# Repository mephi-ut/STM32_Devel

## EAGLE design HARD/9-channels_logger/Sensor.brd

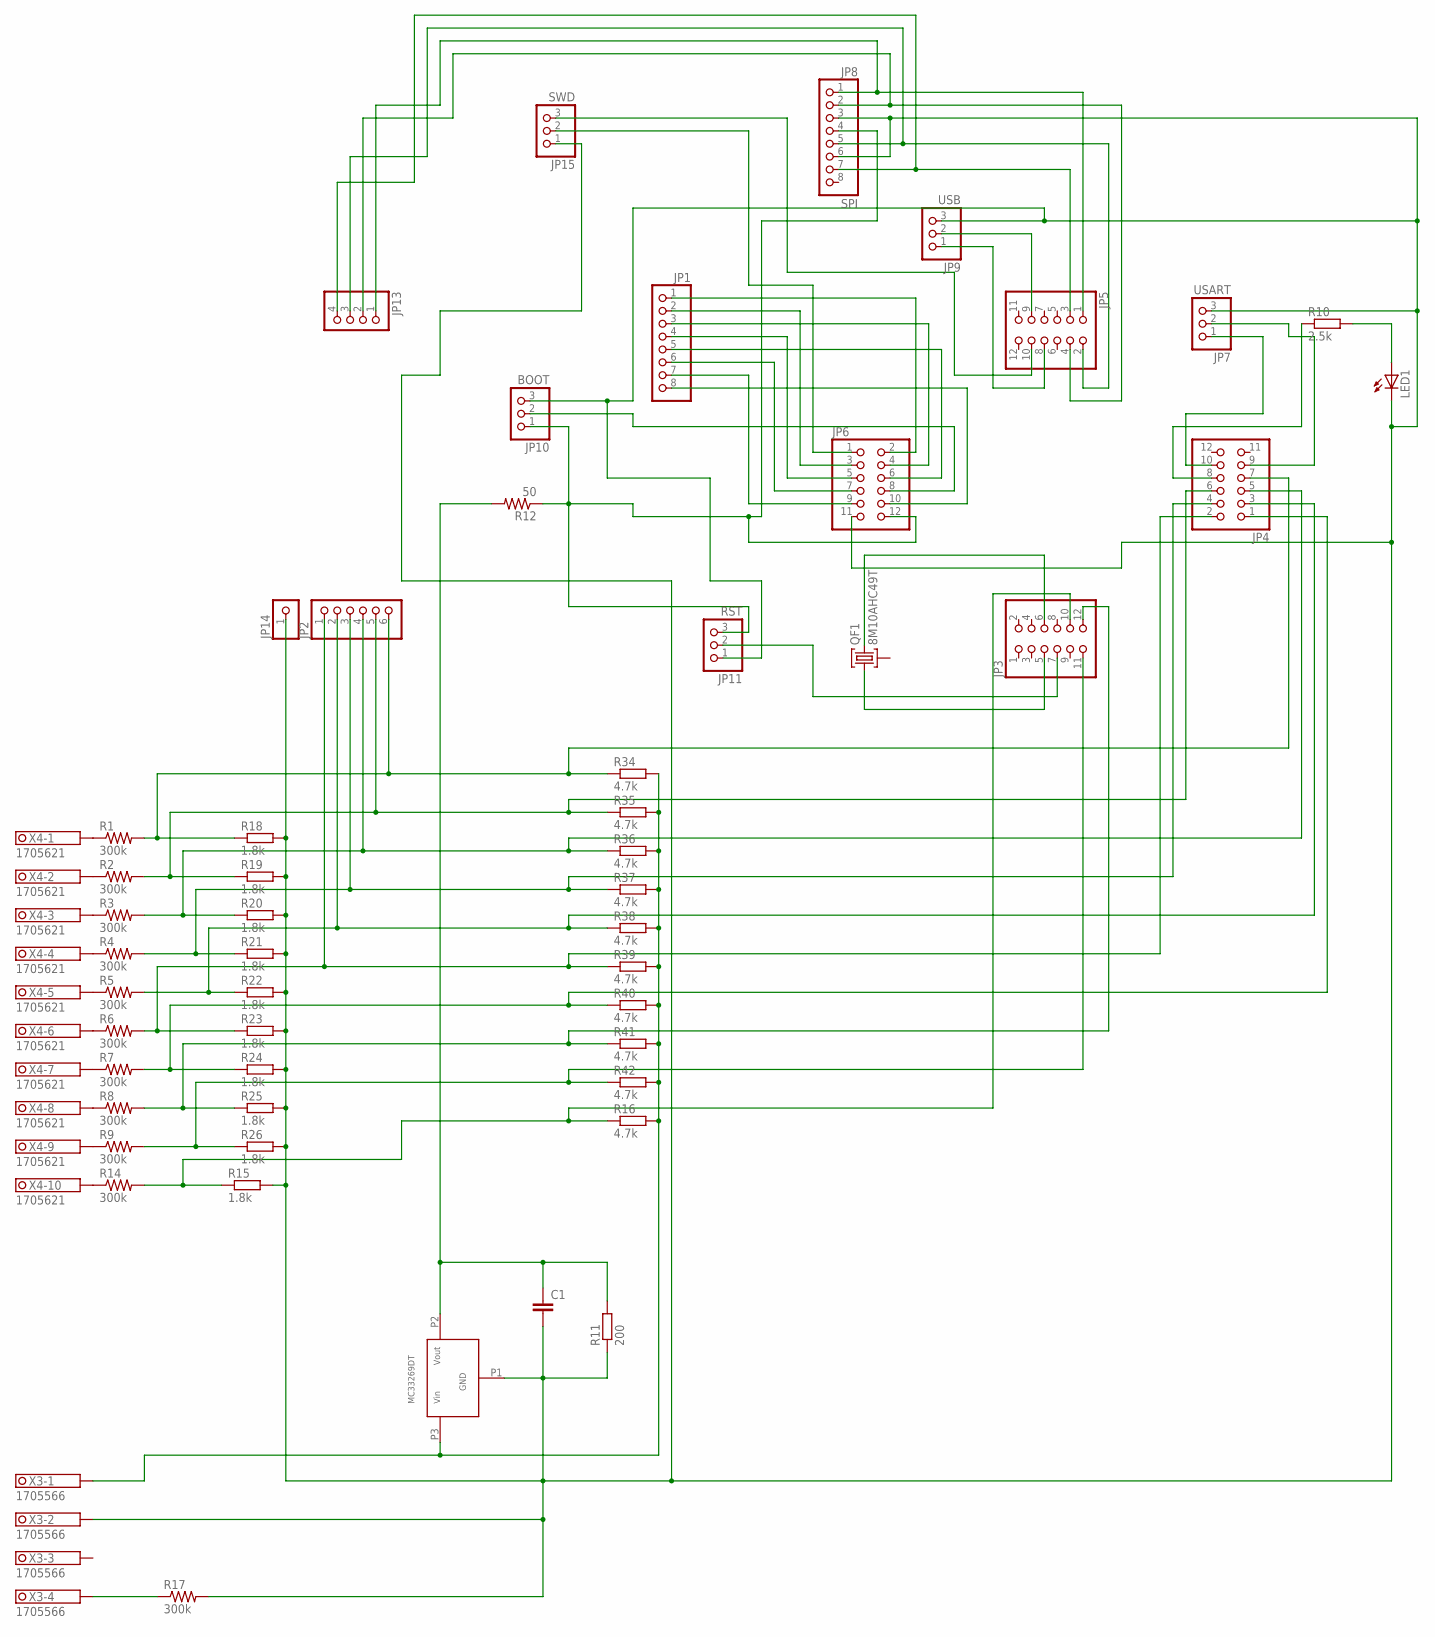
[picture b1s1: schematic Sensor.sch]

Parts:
C1: C2.5/6; C2.5-6
JP1: PINHD-1X8; 1X08
JP2: PINHD-1X6; 1X06
JP3, JP4, JP5, JP6: PINHD-2X6; 2X06
JP7: USART; 1X03
JP8: SPI; 1X08
JP9: USB; 1X03
JP10: BOOT; 1X03
JP11: RST; 1X03
JP13: PINHD-1X4; 1X04
JP14: PINHD-1X1; 1X01
JP15: SWD; 1X03
LED1: LED3MM
QF1: 8M10AHC49T; HC49U
R1, R2, R3, R4, R5, R6, R7, R8, R9, R14, R17: 300k; 0207/15
R10: 2.5k; M1206
R11: 200; R1206
R12: 50; 0207/15
R15, R18, R19, R20, R21, R22, R23, R24, R25, R26: 1.8k; R1206
R16, R34, R35, R36, R37, R38, R39, R40, R41, R42: 4.7k; R1206
U$3: MC33269DT
X3: 1705566
X4: 1705621

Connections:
unnamed: JP3.10, R14.2, R15.1, R16.1
unnamed: R17.1, X3.4.1, X3.4.2
unnamed: R1.1, X4.1.1, X4.1.2
unnamed: R2.1, X4.2.1, X4.2.2
unnamed: R3.1, X4.3.1, X4.3.2
unnamed: R4.1, X4.4.1, X4.4.2
unnamed: R5.1, X4.5.1, X4.5.2
unnamed: R6.1, X4.6.1, X4.6.2
unnamed: R7.1, X4.7.1, X4.7.2
unnamed: JP3.5, QF1.1
unnamed: JP3.6, QF1.3
unnamed: JP3.7, JP11.2
unnamed: R8.1, X4.8.1, X4.8.2
unnamed: LED1.A, R10.2
unnamed: JP4.8, R10.1
unnamed: R16.2, R34.2, R35.2, R36.2, R37.2, R38.2, R39.2, R40.2, R41.2, R42.2, U$3.P3 (VIN), X3.1.1, X3.1.2
unnamed: JP2.6, JP4.7, R1.2, R18.1, R34.1
unnamed: JP2.5, JP4.6, R2.2, R19.1, R35.1
unnamed: JP2.4, JP4.5, R3.2, R20.1, R36.1
unnamed: JP2.3, JP4.4, R4.2, R21.1, R37.1
unnamed: JP2.2, JP4.3, R5.2, R22.1, R38.1
unnamed: JP2.1, JP4.2, R6.2, R23.1, R39.1
unnamed: JP4.1, R7.2, R24.1, R40.1
unnamed: JP3.12, R8.2, R25.1, R41.1
unnamed: JP3.11, R9.2, R26.1, R42.1
unnamed: JP4.9, JP7.2
unnamed: JP4.10, JP7.1
unnamed: C1.2, JP6.11, JP7.3, JP8.3, JP8.6, JP9.3, JP10.3, JP11.1, JP14.1, JP15.1, LED1.K (C), R11.1, R15.2, R17.2, R18.2, R19.2, R20.2, R21.2, R22.2, R23.2, R24.2, R25.2, R26.2, U$3.P1 (GND), X3.2.1, X3.2.2
unnamed: C1.1, R11.2, R12.2, U$3.P2 (VOUT)
unnamed: JP5.8, JP9.1
unnamed: JP5.9, JP9.2
unnamed: JP5.10, JP15.3
unnamed: JP6.1, JP15.2
unnamed: JP5.1, JP8.1, JP13.1
unnamed: JP5.4, JP8.2, JP13.2
unnamed: JP5.2, JP8.5, JP13.3
unnamed: JP5.3, JP8.7, JP13.4
unnamed: JP6.12, JP8.4, JP10.1, JP11.3, R12.1
unnamed: JP1.1, JP6.2
unnamed: JP1.2, JP6.3
unnamed: JP1.3, JP6.4
unnamed: JP1.4, JP6.5
unnamed: JP1.5, JP6.6
unnamed: JP1.6, JP6.7
unnamed: JP1.7, JP6.9
unnamed: JP1.8, JP6.10
unnamed: R9.1, X4.9.1, X4.9.2
unnamed: R14.1, X4.10.1, X4.10.2
unnamed: JP6.8, JP10.2

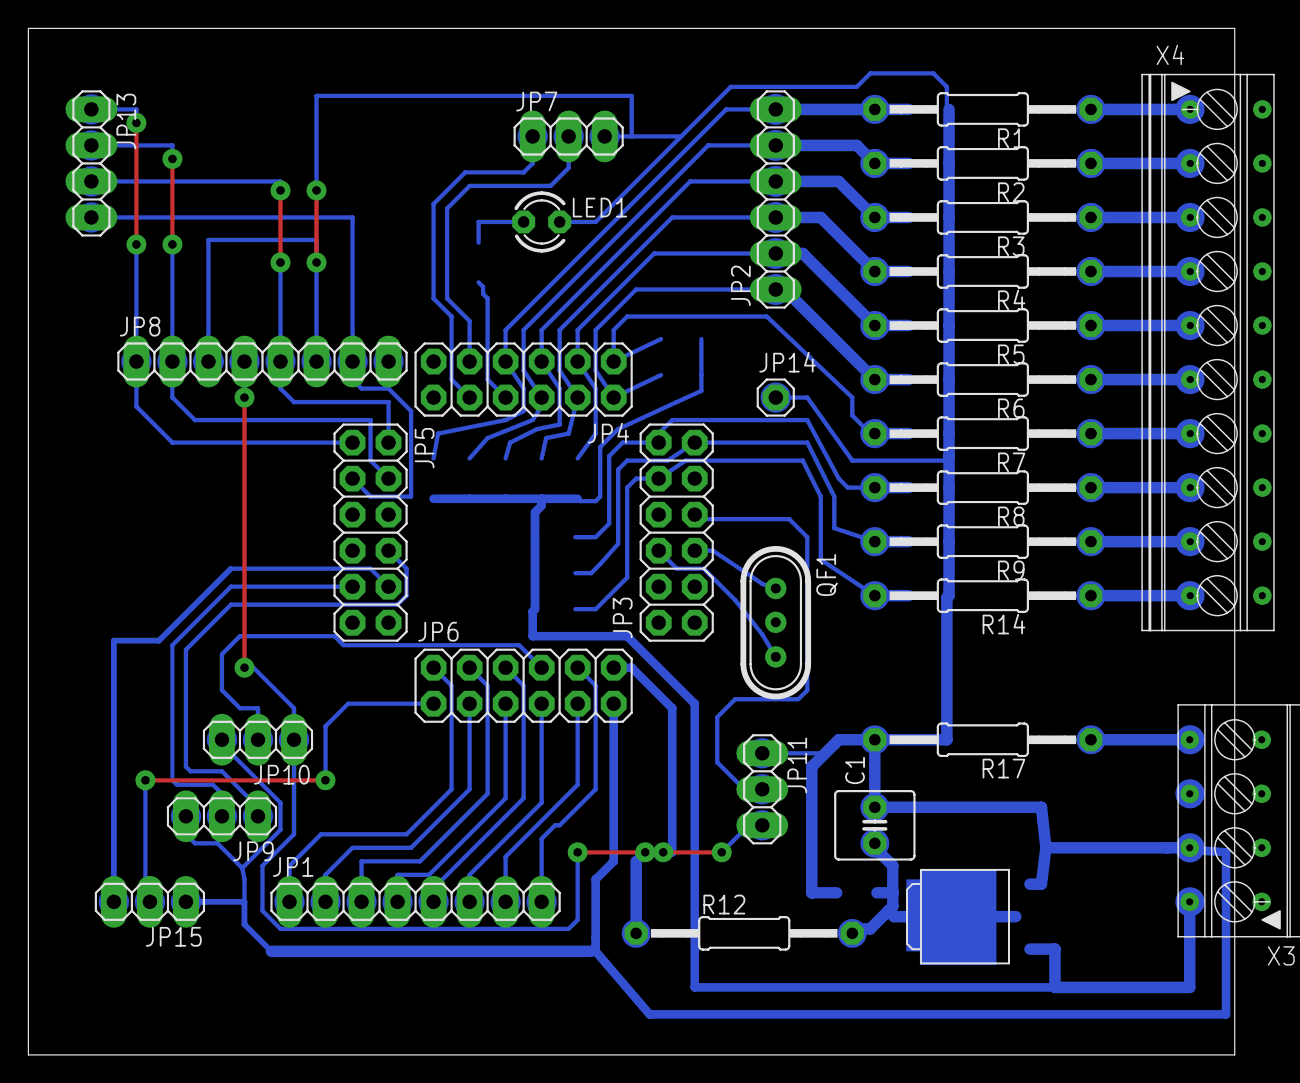
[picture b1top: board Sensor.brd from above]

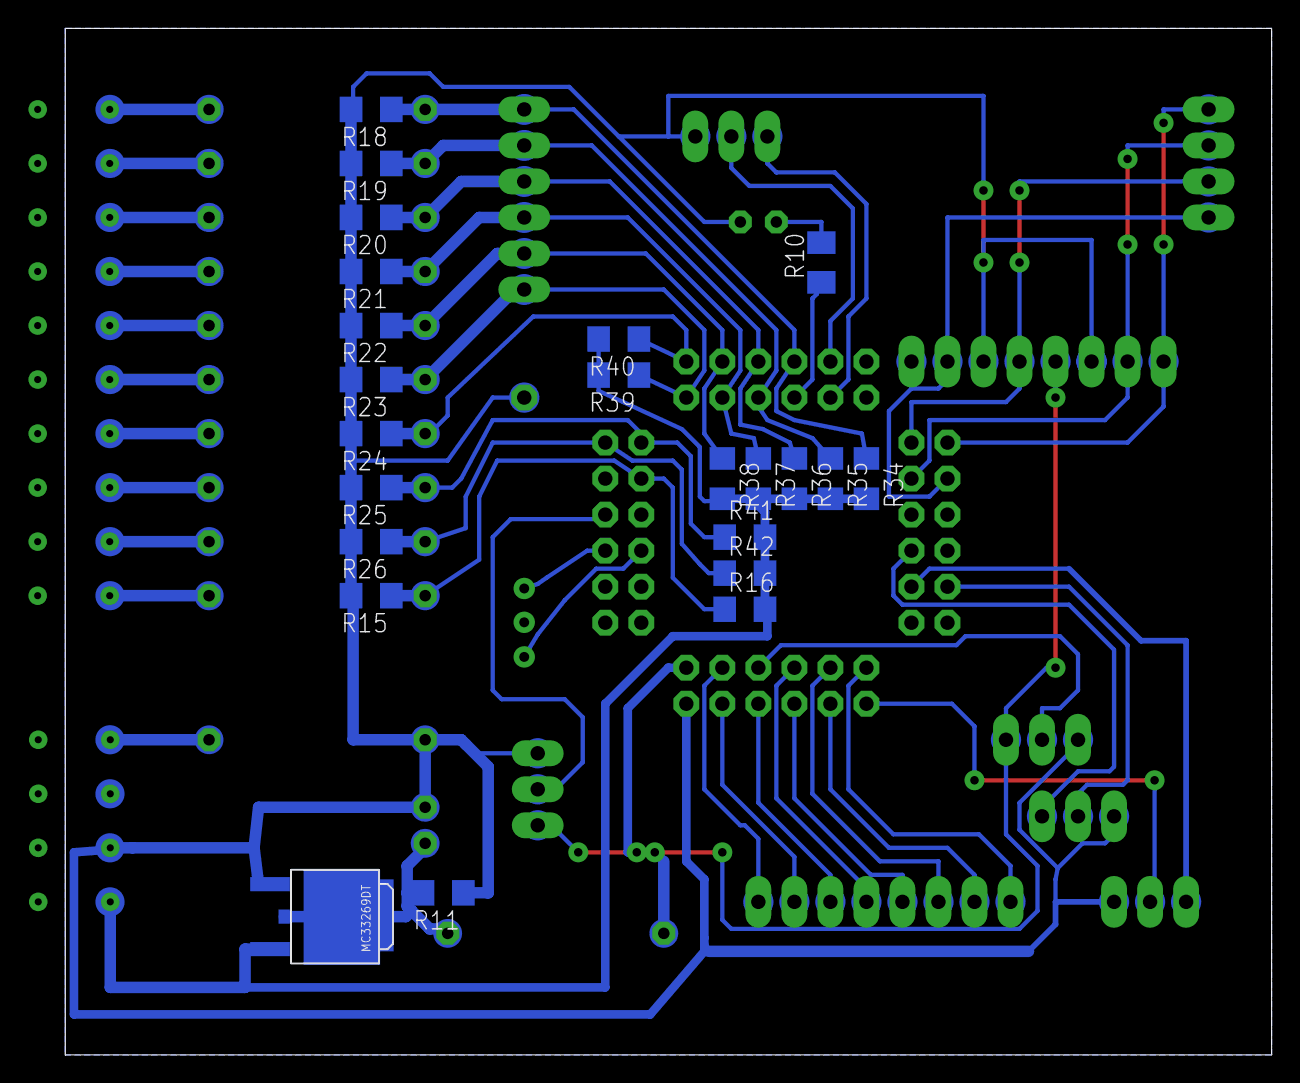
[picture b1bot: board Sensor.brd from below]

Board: 2 copper layers, 85.1 x 72.4 mm, 54 parts (23 on the bottom side), 49 nets.

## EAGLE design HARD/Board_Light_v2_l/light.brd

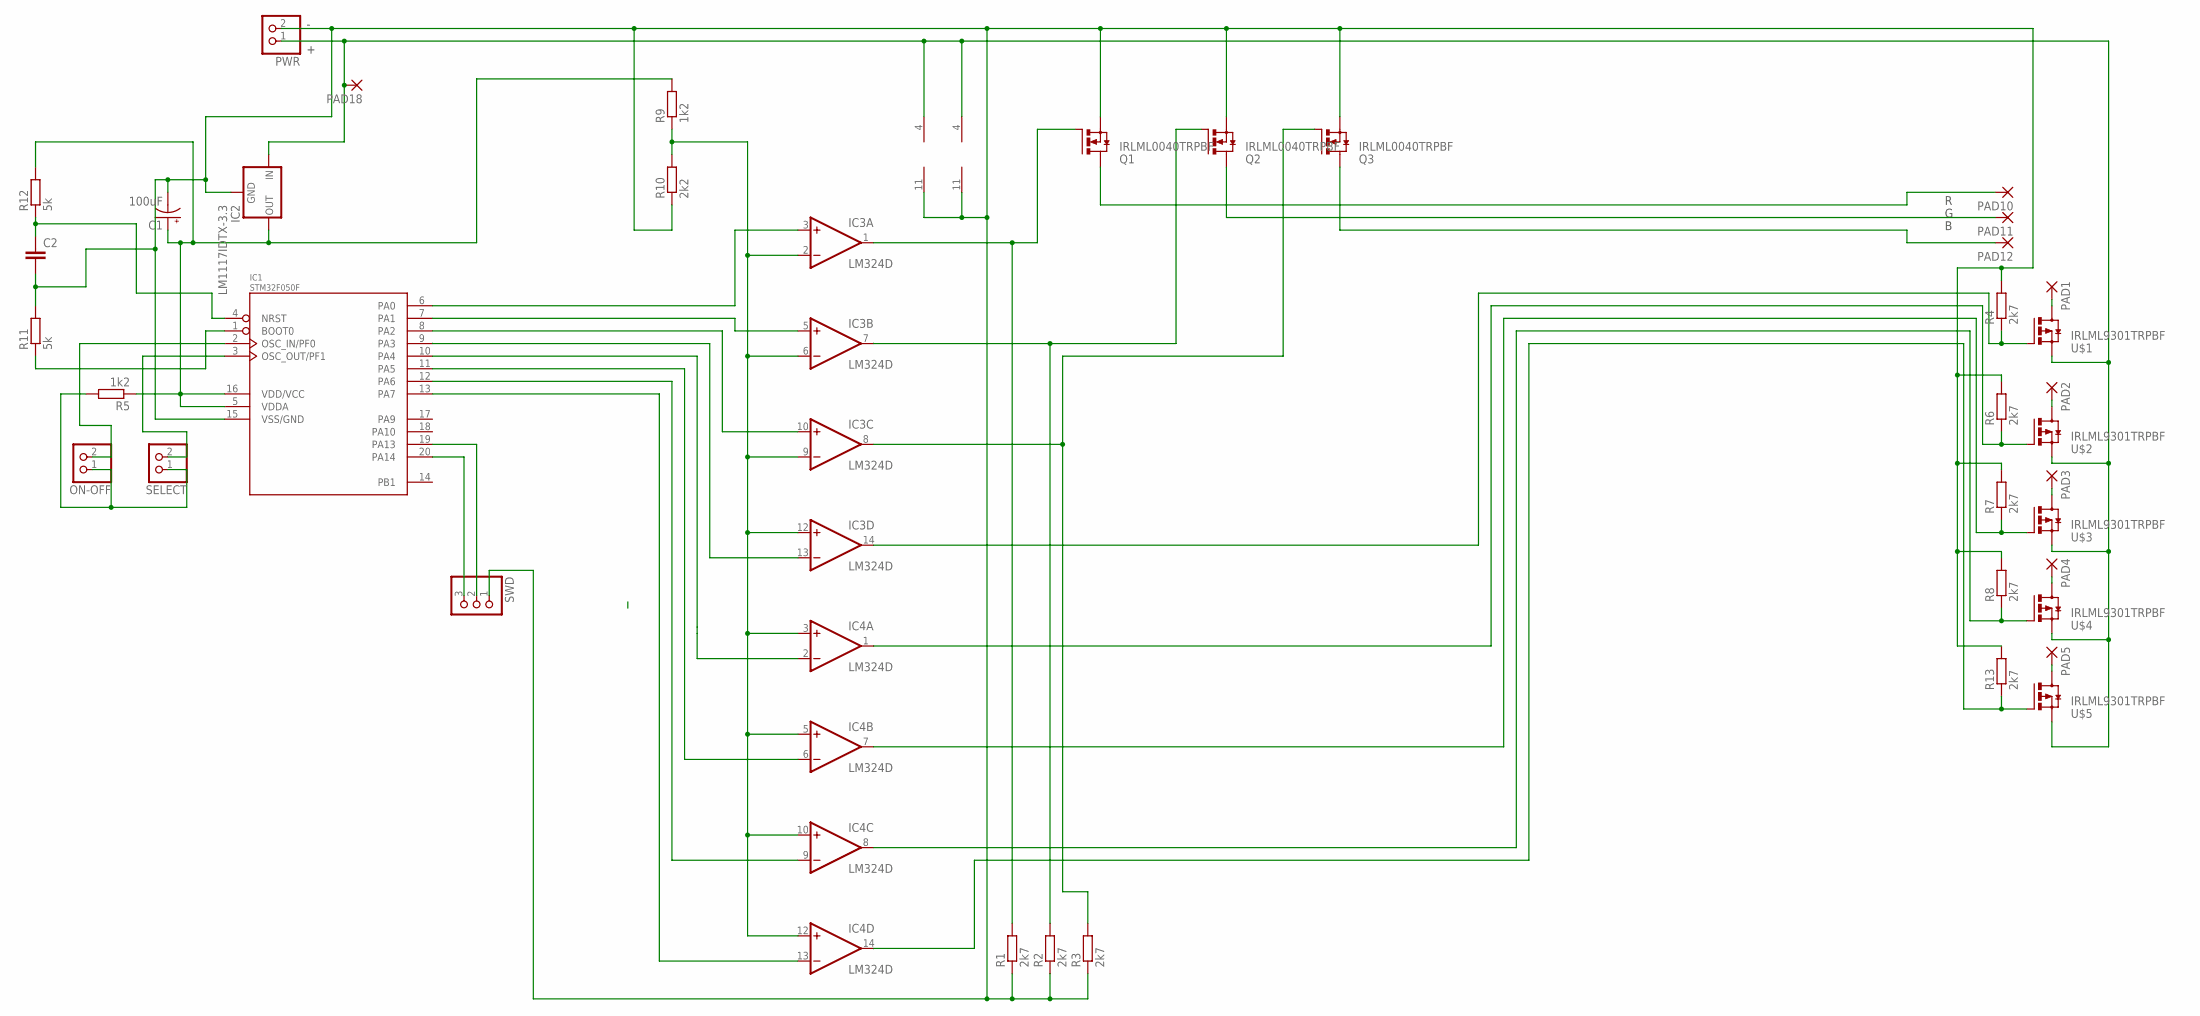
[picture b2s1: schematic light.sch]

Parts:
C1: 100uF; SMC_D
C2: C-EUC1206; C1206
IC1: STM32F050F; TSSOP20
IC2: LM1117IDTX-3.3; TO252
IC3, IC4: LM324D; SO14
ON-OFF: PINHD-1X2; 1X02
PAD1, PAD2, PAD3, PAD4, PAD5, PAD10, PAD11, PAD12, PAD18: SMD2; SMD1,27-2,54
PWR: PINHD-1X2; 1X02
Q1, Q2, Q3: IRLML0040TRPBF; MICRO3
R1, R2, R3, R4, R6, R7, R8, R13: 2k7; M1206
R5, R9: 1k2; M1206
R10: 2k2; M1206
R11, R12: 5k; M1206
SELECT: PINHD-1X2; 1X02
SWD: PINHD-1X3; 1X03
U$1, U$2, U$3, U$4, U$5: IRLML9301TRPBF; MICRO3

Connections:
unnamed: IC3.8 (OUT), Q3.1 (G), R3.2
unnamed: IC3.7 (OUT), Q2.1 (G), R2.2
unnamed: IC3.14 (OUT), R4.1, U$1.1 (G)
unnamed: IC4.1 (OUT), R6.1, U$2.1 (G)
unnamed: IC2.2 (IN), IC3.4 (V+), IC4.4 (V+), PAD18.1, PWR.1, U$1.2 (S), U$2.2 (S), U$3.2 (S), U$4.2 (S), U$5.2 (S)
unnamed: ON-OFF.1, R5.2, SELECT.1
unnamed: PAD10.1, Q1.3 (D)
unnamed: PAD11.1, Q2.3 (D)
unnamed: PAD12.1, Q3.3 (D)
unnamed: IC4.7 (OUT), R7.1, U$3.1 (G)
unnamed: IC4.8 (OUT), R8.1, U$4.1 (G)
unnamed: IC4.14 (OUT), R13.1, U$5.1 (G)
unnamed: IC1.6 (PA0), IC3.3 (+IN)
unnamed: IC1.7 (PA1), IC3.5 (+IN)
unnamed: IC1.8 (PA2), IC3.10 (+IN)
unnamed: IC1.9 (PA3), IC3.13 (-IN)
unnamed: IC1.10 (PA4), IC4.2 (-IN)
unnamed: IC1.11 (PA5), IC4.6 (-IN)
unnamed: IC1.12 (PA6), IC4.9 (-IN)
unnamed: IC1.13 (PA7), IC4.13 (-IN)
unnamed: PAD1.1, U$1.3 (D)
unnamed: PAD2.1, U$2.3 (D)
unnamed: PAD3.1, U$3.3 (D)
unnamed: IC3.2 (-IN), IC3.6 (-IN), IC3.9 (-IN), IC3.12 (+IN), IC4.3 (+IN), IC4.5 (+IN), IC4.10 (+IN), IC4.12 (+IN), R9.1, R10.2
unnamed: PAD4.1, U$4.3 (D)
unnamed: PAD5.1, U$5.3 (D)
unnamed: C2.1, IC1.4 (NRST), R12.1
unnamed: IC1.1 (BOOT0), R11.1
unnamed: IC1.19 (PA13), SWD.2
unnamed: IC1.20 (PA14), SWD.3
unnamed: IC1.2 (OSC_IN/PF0), ON-OFF.2
unnamed: IC3.1 (OUT), Q1.1 (G), R1.2
unnamed: C1.+, IC1.5 (VDDA), IC1.16 (VDD/VCC), IC2.TAB (OUT), R5.1, R9.2, R12.2
unnamed: C1.-, C2.2, IC1.15 (VSS/GND), IC2.1 (GND), IC3.11 (V-), IC4.11 (V-), PWR.2, Q1.2 (S), Q2.2 (S), Q3.2 (S), R1.1, R2.1, R3.1, R4.2, R6.2, R7.2, R8.2, R10.1, R11.2, R13.2, SWD.1
unnamed: IC1.3 (OSC_OUT/PF1), SELECT.2

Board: 2 copper layers, 40 parts (3 on the bottom side), 35 nets, no tracks yet.

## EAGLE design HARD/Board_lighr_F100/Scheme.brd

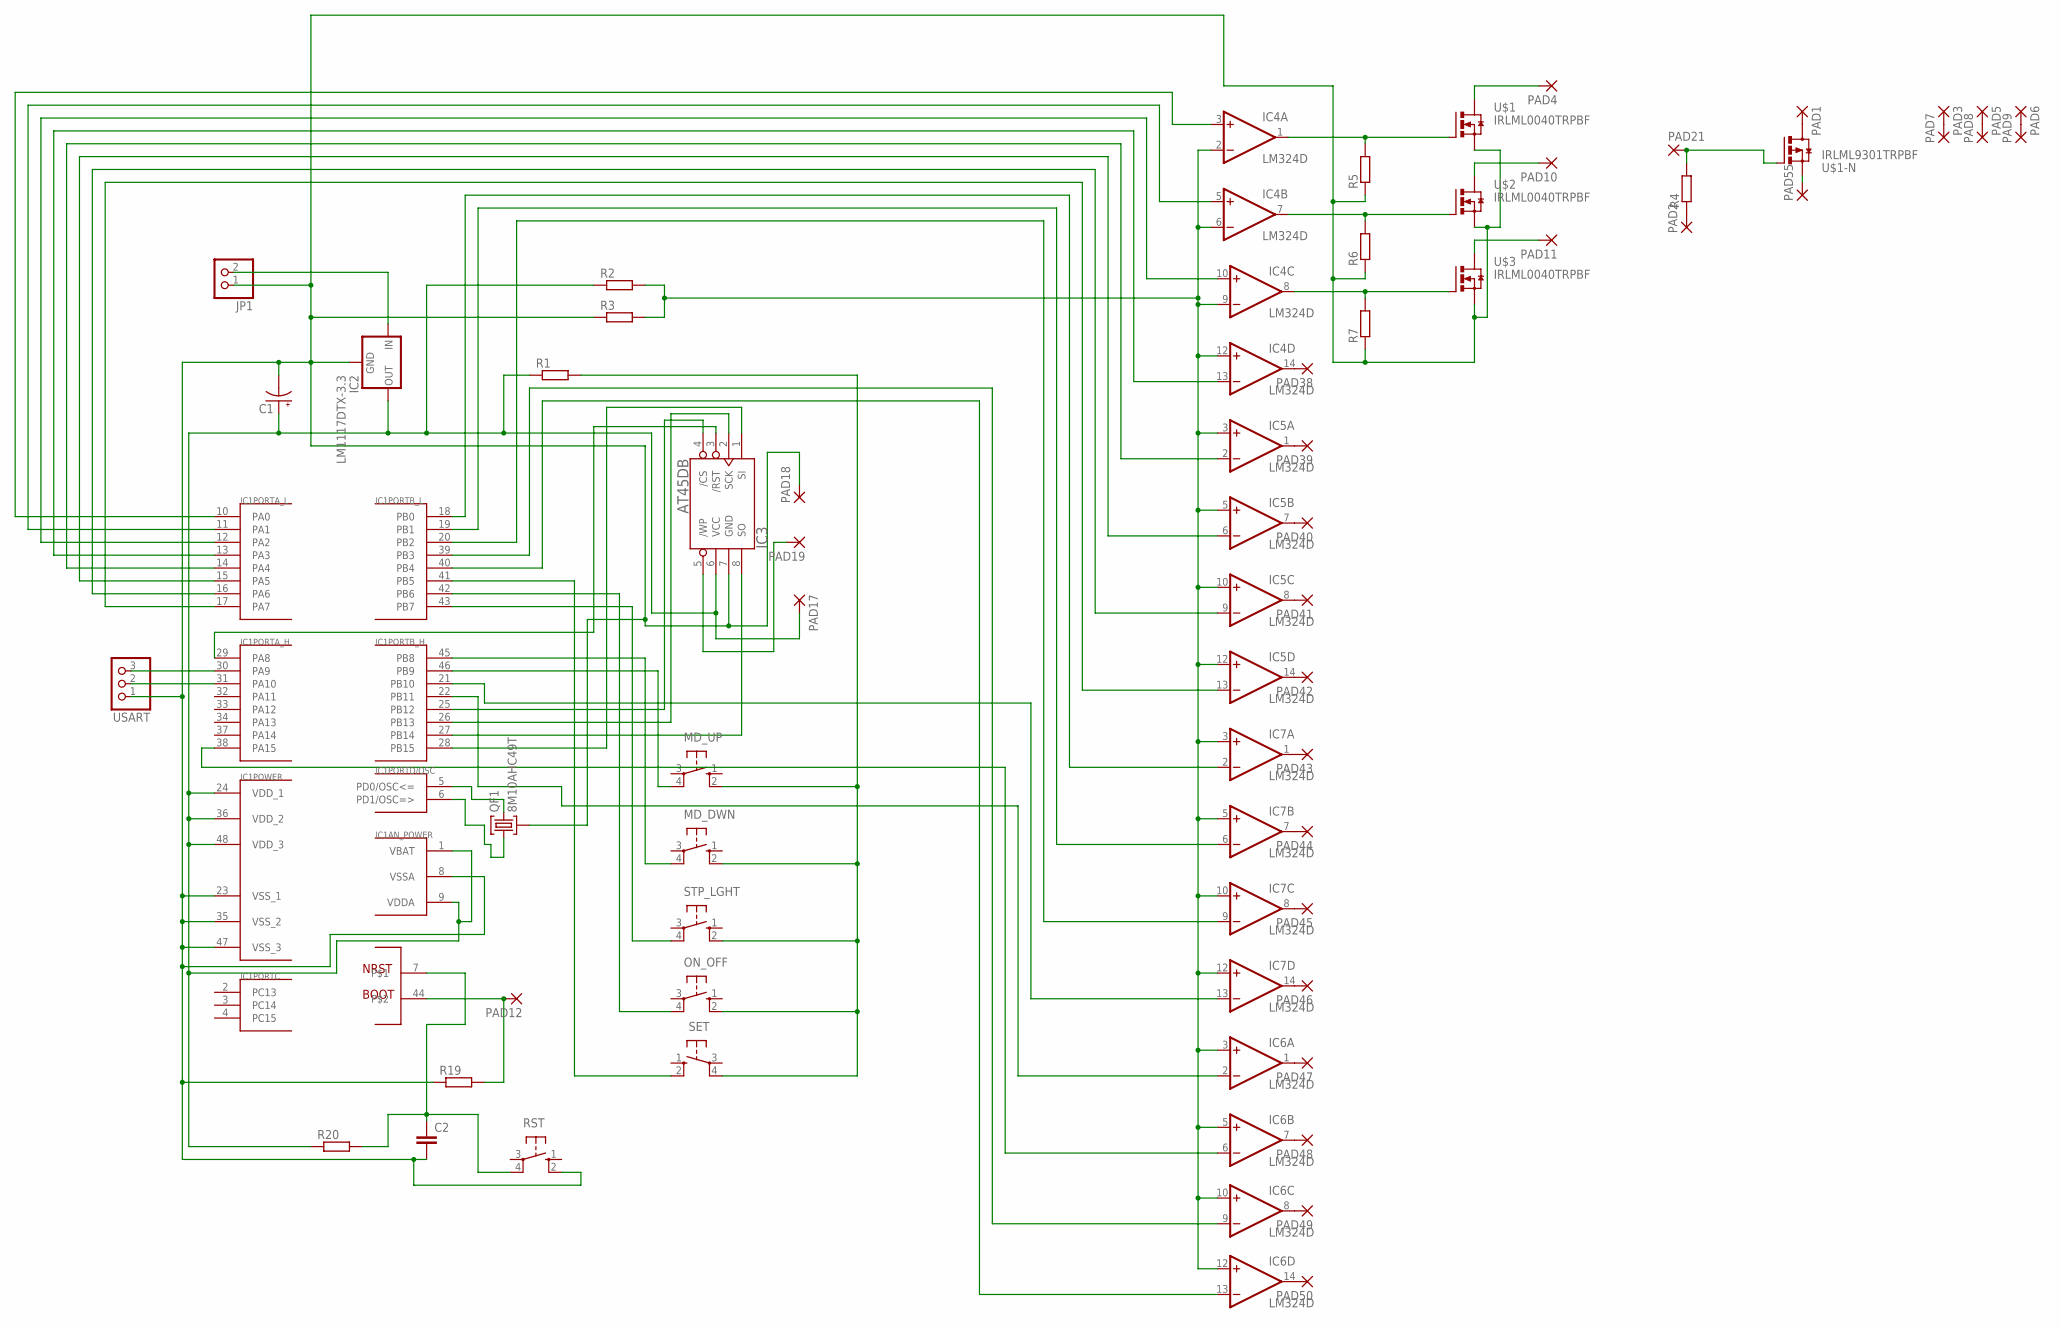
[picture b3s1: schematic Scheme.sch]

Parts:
C1: CPOL-USSMCD; SMC_D
C2: C-EUC0805; C0805
IC1: STM32F10XCXT6; TQFP48
IC2: LM1117DTX-3.3; TO252
IC3: AT45DB-S; SOIC8_208MIL
IC4, IC5, IC6, IC7: LM324D; SO14
JP1: PINHD-1X2; 1X02
MD_DWN: 40-XX; B3F-40XX
MD_UP: 40-XX; B3F-40XX
ON_OFF: 40-XX; B3F-40XX
PAD1, PAD2, PAD3, PAD4, PAD5, PAD6, PAD7, PAD8, PAD9, PAD10, PAD11, PAD12, PAD17, PAD18, PAD19, PAD21, PAD38, PAD39, PAD40, PAD41, PAD42, PAD43, PAD44, PAD45, PAD46, PAD47, PAD48, PAD49, PAD50, PAD55: SMD2; SMD1,27-2,54
QF1: 8M10AHC49T; HC49U
R1, R2, R3, R4, R5, R6, R7, R19, R20: R-EU_R1206; R1206
RST: 40-XX; B3F-40XX
SET: 40-XX; B3F-40XX
STP_LGHT: 40-XX; B3F-40XX
U$1, U$2, U$3: IRLML0040TRPBF; MICRO3
U$1-N: IRLML9301TRPBF; MICRO3
USART: PINHD-1X3; 1X03

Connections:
unnamed: PAD2.1, R4.1
unnamed: C1.-, C2.2, IC1.8 (VSSA), IC1.23 (VSS_1), IC1.35 (VSS_2), IC1.47 (VSS_3), IC2.1 (GND), IC3.7 (GND), JP1.1, PAD18.1, QF1.2, R3.1, R5.1, R6.1, R7.1, R19.1, RST.2 (S1), U$1.2 (S), U$2.2 (S), U$3.2 (S), USART.1
unnamed: PAD21.1, R4.2, U$1-N.1 (G)
unnamed: IC1.38 (PA15), IC6.6 (-IN)
unnamed: IC1.39 (PB3), IC6.9 (-IN)
unnamed: IC1.40 (PB4), IC6.13 (-IN)
unnamed: IC1.46 (PB9), MD_UP.4 (P1)
unnamed: IC1.45 (PB8), MD_DWN.4 (P1)
unnamed: IC1.43 (PB7), STP_LGHT.4 (P1)
unnamed: MD_DWN.2 (S1), MD_UP.2 (S1), ON_OFF.2 (S1), R1.2, SET.4 (P1), STP_LGHT.2 (S1)
unnamed: IC1.42 (PB6), ON_OFF.4 (P1)
unnamed: IC4.1 (OUT), R5.2, U$1.1 (G)
unnamed: IC4.7 (OUT), R6.2, U$2.1 (G)
unnamed: IC1.25 (PB12), IC3.4 (/CS)
unnamed: IC1.10 (PA0), IC4.3 (+IN)
unnamed: IC1.11 (PA1), IC4.5 (+IN)
unnamed: IC1.12 (PA2), IC4.10 (+IN)
unnamed: IC1.13 (PA3), IC4.13 (-IN)
unnamed: IC1.14 (PA4), IC5.2 (-IN)
unnamed: IC1.15 (PA5), IC5.6 (-IN)
unnamed: IC1.16 (PA6), IC5.9 (-IN)
unnamed: IC1.17 (PA7), IC5.13 (-IN)
unnamed: IC1.18 (PB0), IC7.2 (-IN)
unnamed: IC1.19 (PB1), IC7.6 (-IN)
unnamed: IC1.20 (PB2), IC7.9 (-IN)
unnamed: IC1.21 (PB10), IC7.13 (-IN)
unnamed: IC1.22 (PB11), IC6.2 (-IN)
unnamed: IC1.26 (PB13), IC3.2 (SCK)
unnamed: IC1.27 (PB14), IC3.8 (SO)
unnamed: IC1.28 (PB15), IC3.1 (SI)
unnamed: IC4.2 (-IN), IC4.6 (-IN), IC4.9 (-IN), IC4.12 (+IN), IC5.3 (+IN), IC5.5 (+IN), IC5.10 (+IN), IC5.12 (+IN), IC6.3 (+IN), IC6.5 (+IN), IC6.10 (+IN), IC6.12 (+IN), IC7.3 (+IN), IC7.5 (+IN), IC7.10 (+IN), IC7.12 (+IN), R2.2, R3.2
unnamed: C1.+, IC1.1 (VBAT), IC1.9 (VDDA), IC1.24 (VDD_1), IC1.36 (VDD_2), IC1.48 (VDD_3), IC2.TAB (OUT), IC3.6 (VCC), PAD17.1, R1.1, R2.1, R20.1
unnamed: IC4.8 (OUT), R7.2, U$3.1 (G)
unnamed: PAD1.1, U$1-N.3 (D)
unnamed: IC1.41 (PB5), SET.2 (S1)
unnamed: PAD3.1, PAD7.1
unnamed: PAD5.1, PAD8.1
unnamed: PAD6.1, PAD9.1
unnamed: IC1.30 (PA9), USART.3
unnamed: PAD4.1, U$1.3 (D)
unnamed: PAD10.1, U$2.3 (D)
unnamed: PAD11.1, U$3.3 (D)
unnamed: IC1.31 (PA10), USART.2
unnamed: IC1.44, PAD12.1, R19.2
unnamed: IC1.29 (PA8), IC3.3 (/RST)
unnamed: C2.1, IC1.7, R20.2, RST.4 (P1)
unnamed: IC3.5 (/WP), PAD19.1
unnamed: IC1.5 (PD0/OSC<=), QF1.3
unnamed: IC1.6 (PD1/OSC=>), QF1.1
unnamed: IC4.14 (OUT), PAD38.1
unnamed: IC5.1 (OUT), PAD39.1
unnamed: IC5.7 (OUT), PAD40.1
unnamed: IC5.8 (OUT), PAD41.1
unnamed: IC5.14 (OUT), PAD42.1
unnamed: IC7.1 (OUT), PAD43.1
unnamed: IC7.7 (OUT), PAD44.1
unnamed: IC7.14 (OUT), PAD46.1
unnamed: IC6.1 (OUT), PAD47.1
unnamed: IC6.7 (OUT), PAD48.1
unnamed: IC6.8 (OUT), PAD49.1
unnamed: IC6.14 (OUT), PAD50.1
unnamed: IC7.8 (OUT), PAD45.1
unnamed: IC2.2 (IN), JP1.2
unnamed: PAD55.1, U$1-N.2 (S)
V+: IC4.4 (V+), IC5.4 (V+), IC6.4 (V+), IC7.4 (V+)
V-: IC4.11 (V-), IC5.11 (V-), IC6.11 (V-), IC7.11 (V-)

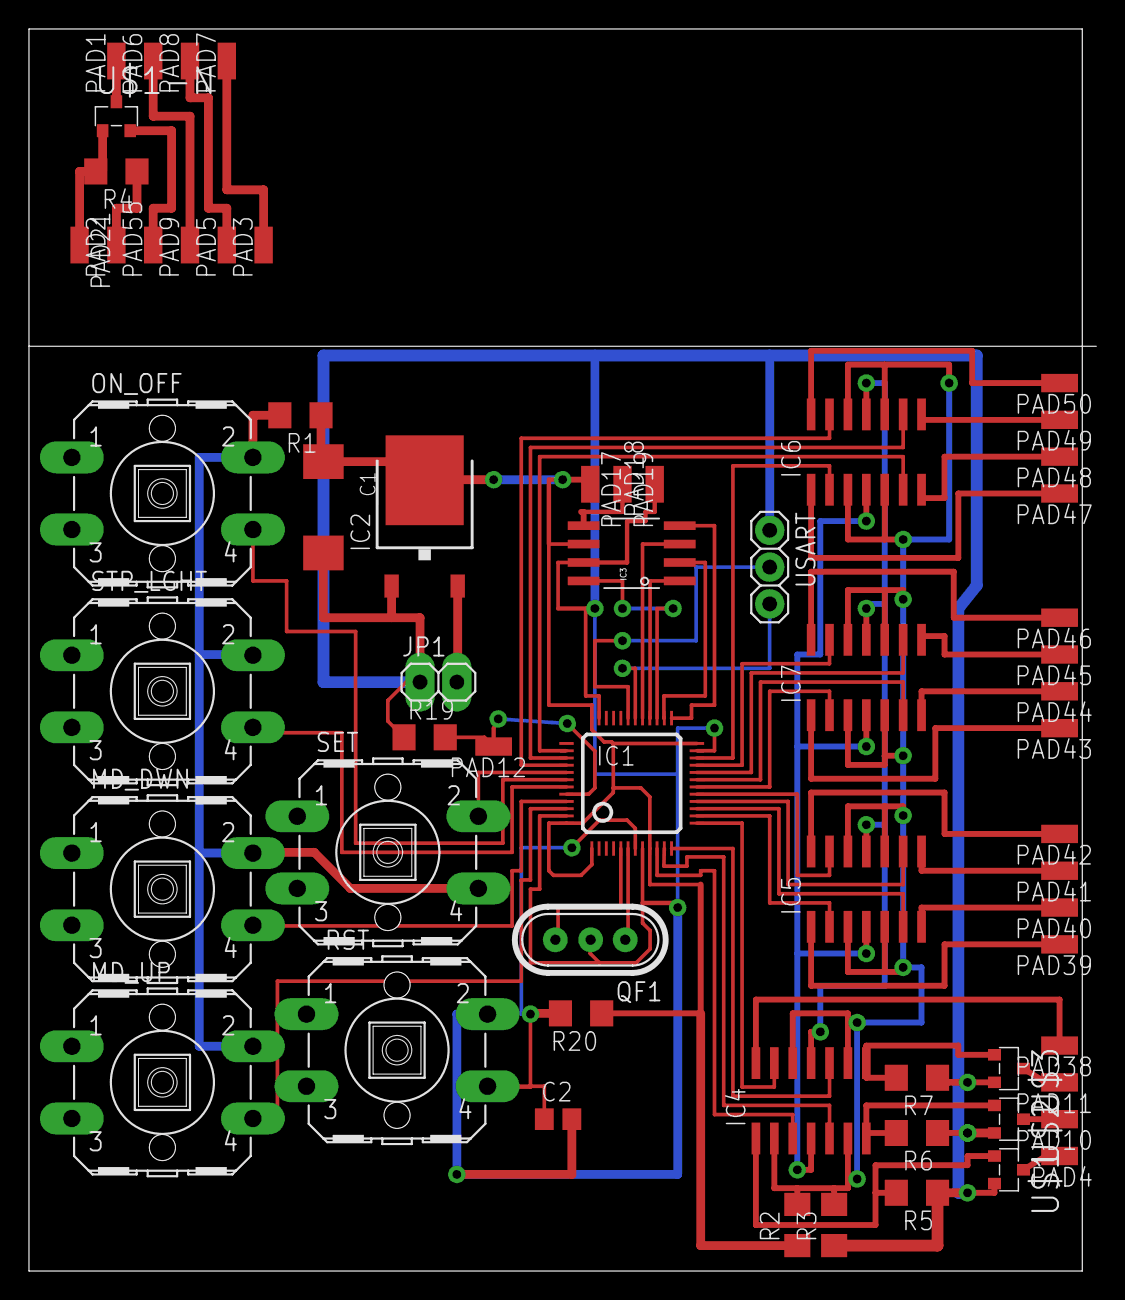
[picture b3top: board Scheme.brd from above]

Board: 2 copper layers, 73.7 x 85.7 mm, 61 parts (0 on the bottom side), 66 nets.

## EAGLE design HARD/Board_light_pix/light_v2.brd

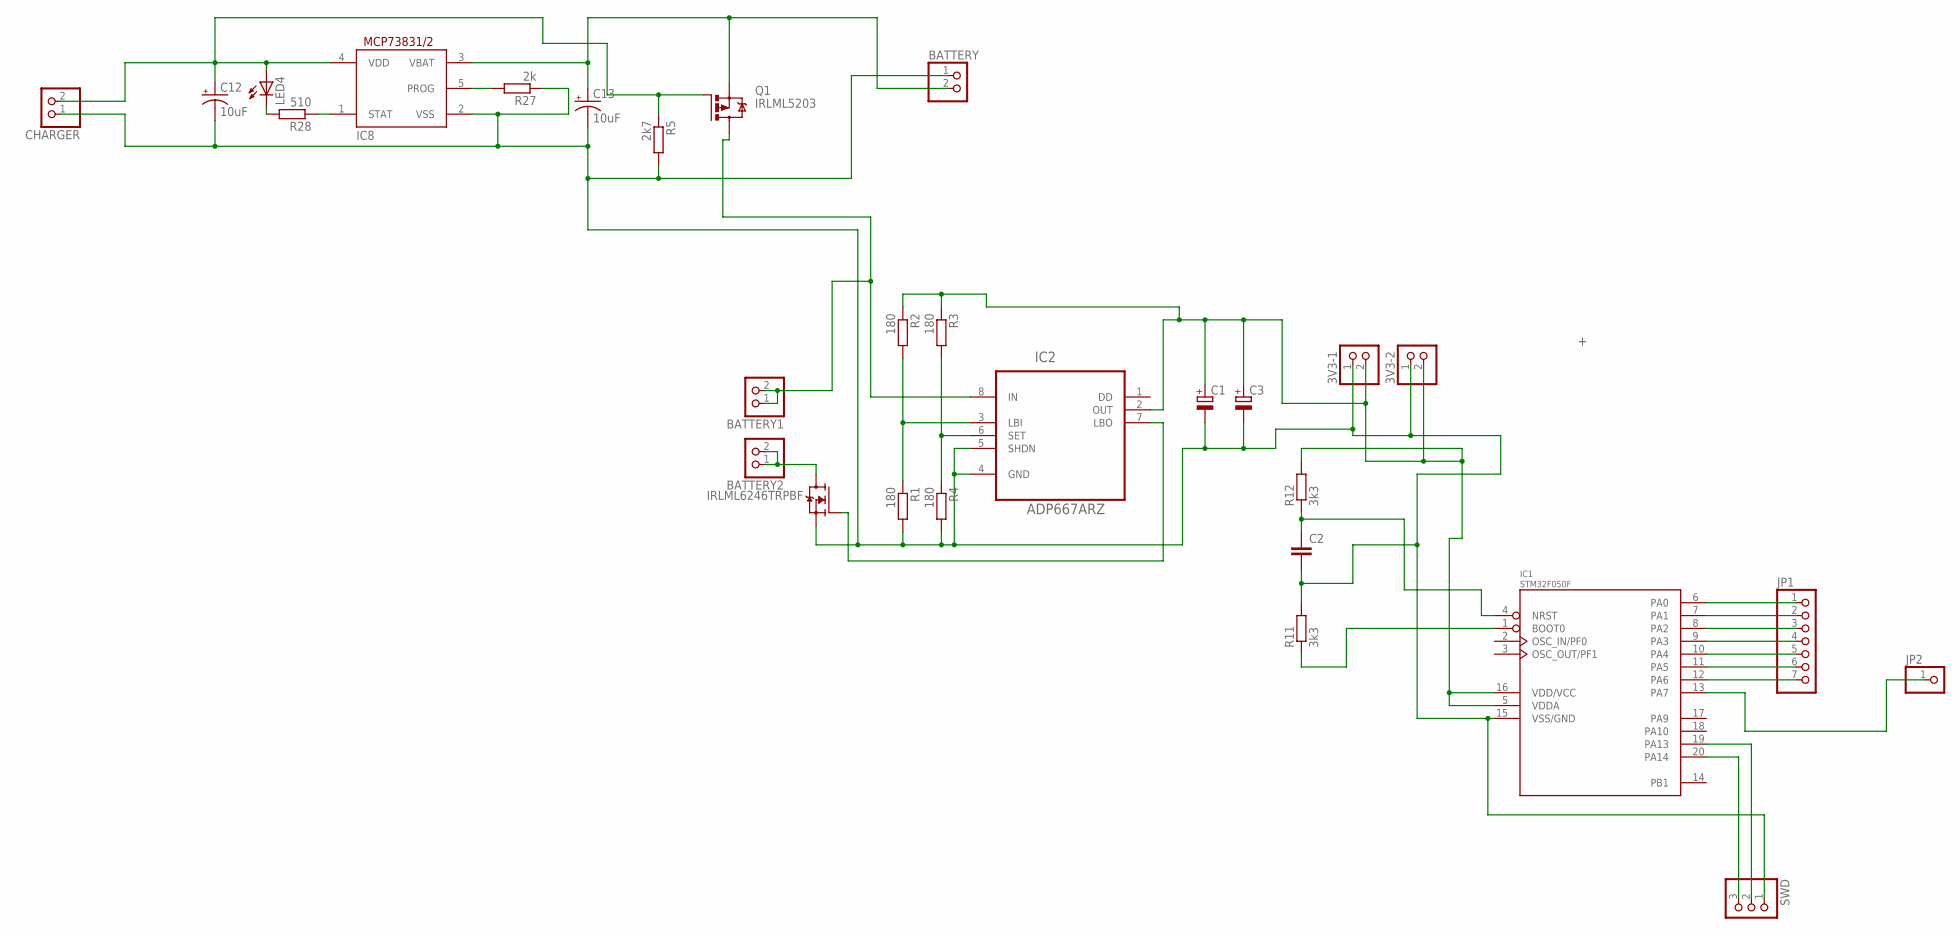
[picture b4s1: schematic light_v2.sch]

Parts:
3V3-1, 3V3-2: PINHD-1X2; 1X02
BATTERY, BATTERY1, BATTERY2: PINHD-1X2; 1X02
C1, C3: CPOL-EUSMCD; SMC_D
C2: C-EUC1206; C1206
C12, C13: 10uF; SMC_D
CHARGER: PINHD-1X2; 1X02
IC1: STM32F050F; TSSOP20
IC2: ADP667ARZ; SOIC127P600X175-8N
IC8: MCP73831/OT; SOT23-5L
IRLML6246TRPBF: MOSFET-N-SOT23; SOT23
JP1: PINHD-1X7; 1X07
JP2: PINHD-1X1; 1X01
LED4: LED; SMARTLED-TTW
Q1: IRLML5203; MICRO3
R1, R2, R3, R4: 180; M1206
R5: 2k7; M1206
R11, R12: 3k3; M1206
R27: 2k; M1206
R28: 510; M1206
SWD: PINHD-1X3; 1X03

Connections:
unnamed: IC1.6 (PA0), JP1.1
unnamed: IC1.7 (PA1), JP1.2
unnamed: IC1.8 (PA2), JP1.3
unnamed: BATTERY1.1, BATTERY1.2, IC2.8 (IN), Q1.3 (D)
unnamed: IC1.9 (PA3), JP1.4
unnamed: IC1.10 (PA4), JP1.5
unnamed: IC1.11 (PA5), JP1.6
unnamed: IC1.12 (PA6), JP1.7
unnamed: IC1.13 (PA7), JP2.1
unnamed: BATTERY2.1, BATTERY2.2, IRLML6246TRPBF.3 (D)
unnamed: IC2.7 (LBO), IRLML6246TRPBF.1 (G)
unnamed: 3V3-1.1, 3V3-2.1, BATTERY.1, C1.-, C2.2, C3.-, C12.-, C13.-, CHARGER.1, IC1.15 (VSS/GND), IC2.4 (GND), IC2.5 (SHDN), IC8.2 (VSS), IRLML6246TRPBF.2 (S), R1.2, R4.2, R5.2, R11.2, R27.1, SWD.1
unnamed: BATTERY.2, C13.+, IC8.3 (VBAT), Q1.2 (S)
unnamed: IC2.6 (SET), R3.2, R4.1
unnamed: IC2.3 (LBI), R1.1, R2.2
unnamed: C2.1, IC1.4 (NRST), R12.1
unnamed: IC1.1 (BOOT0), R11.1
unnamed: IC1.19 (PA13), SWD.2
unnamed: IC1.20 (PA14), SWD.3
unnamed: C12.+, CHARGER.2, IC8.4 (VDD), LED4.A@1 (A), Q1.1 (G), R5.1
unnamed: IC8.5 (PROG), R27.2
unnamed: IC8.1 (STAT), R28.1
unnamed: LED4.C@1 (C), R28.2
OUT: 3V3-1.2, 3V3-2.2, C1.+, C3.+, IC1.5 (VDDA), IC1.16 (VDD/VCC), IC2.2 (OUT), R2.1, R3.1, R12.2

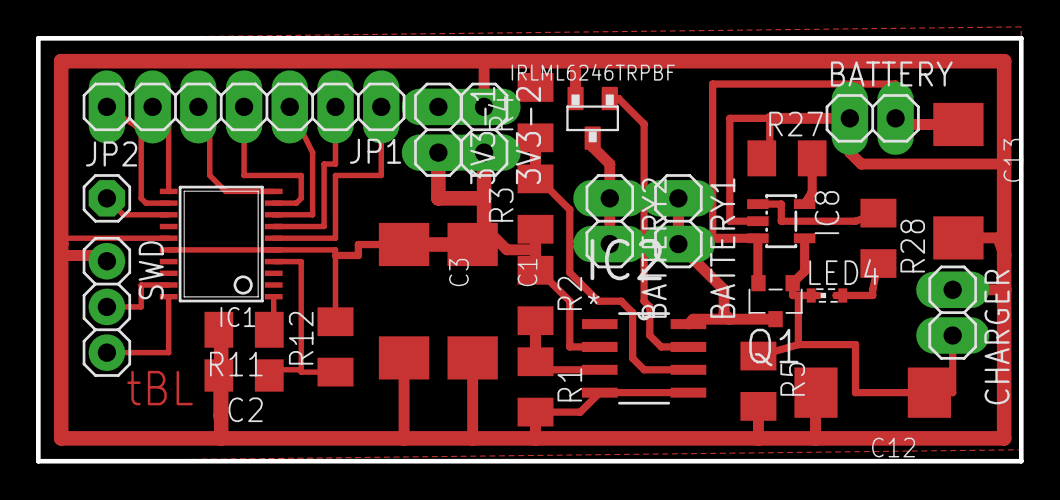
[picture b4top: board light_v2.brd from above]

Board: 2 copper layers, 54.6 x 23.5 mm, 29 parts (0 on the bottom side), 24 nets.

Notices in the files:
parts and their libraries:
SparkFun: Licensing: CC v3.0 Share-Alike You are welcome to use this library for commercial purposes.
